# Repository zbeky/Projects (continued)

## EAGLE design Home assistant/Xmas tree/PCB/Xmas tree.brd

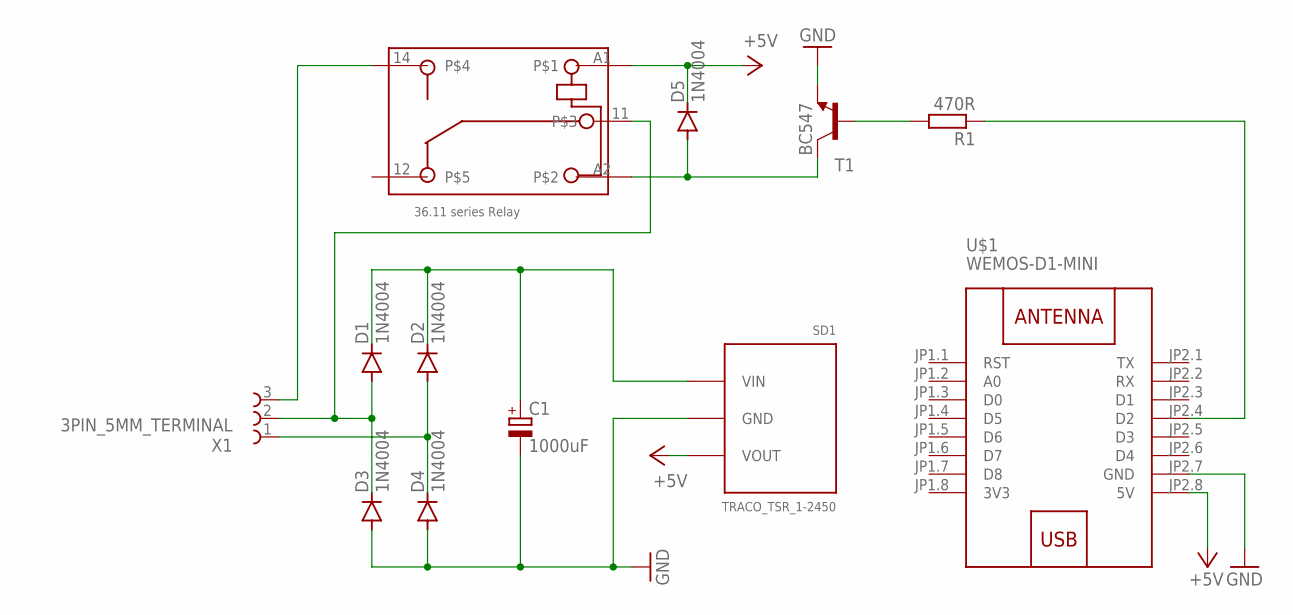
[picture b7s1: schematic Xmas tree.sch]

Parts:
C1: 1000uF; E3,5-10
D1, D2, D3, D4, D5: 1N4004; DO41-10
R1: 470R; 0207/10
RL1: 36.11
SD1: TRACO_TSR_1-2450
T1: BC547; TO92-CBE
U$1: WEMOS-D1-MINI
X1: 3PIN_5MM_TERMINAL

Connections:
3V3: U$1.JP1.8 (3V3)
12VDC: C1.+, D1.C, D2.C, SD1.VIN
+5V: D5.C, RL1.A1, SD1.VOUT, U$1.JP2.8 (5V)
+12VAC: D1.A, D3.C, RL1.11, X1.2
-12VAC: D2.A, D4.C, X1.1
GND: C1.-, D3.A, D4.A, SD1.GND, T1.E, U$1.JP2.7 (GND)
unnamed: R1.2, T1.B
unnamed: D5.A, RL1.A2, T1.C
unnamed: R1.1, U$1.JP2.4 (D2)
OUTPUT: RL1.14, X1.3

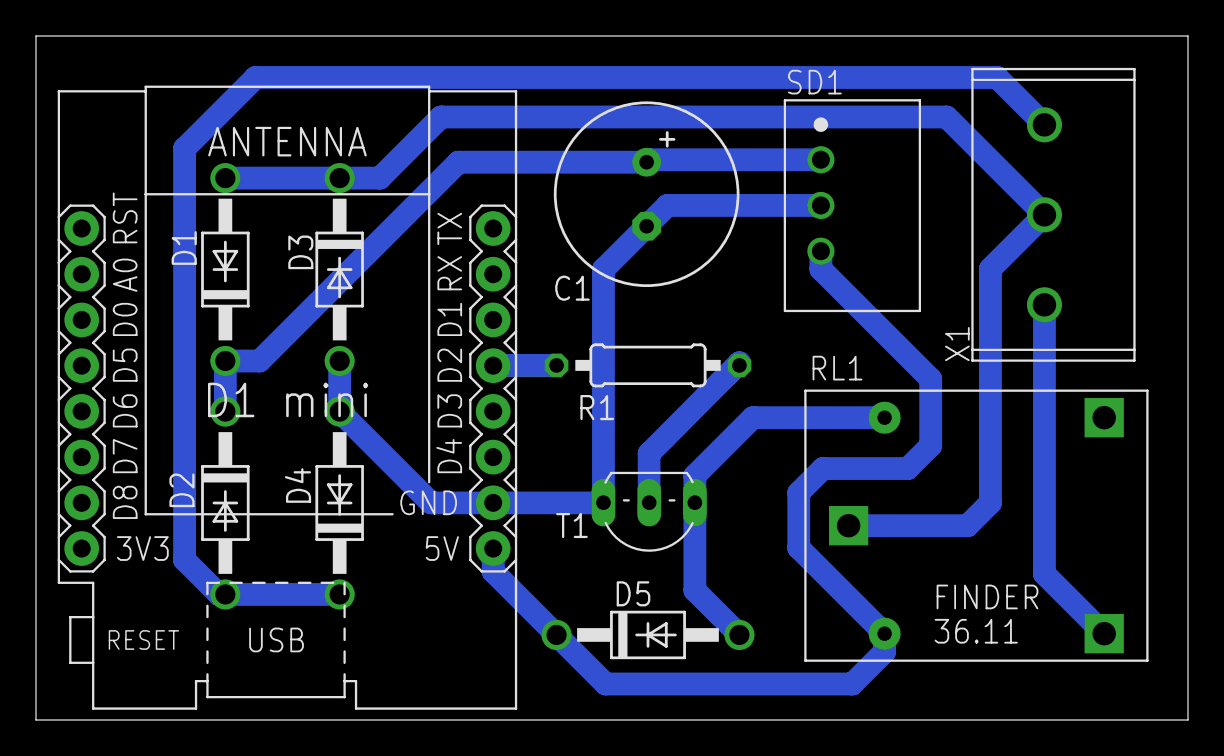
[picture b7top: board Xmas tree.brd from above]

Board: 2 copper layers, 64.0 x 38.0 mm, 12 parts (0 on the bottom side), 9 nets.

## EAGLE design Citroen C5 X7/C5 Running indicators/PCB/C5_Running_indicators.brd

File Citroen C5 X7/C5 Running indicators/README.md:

# Citroen C5 X7 front running indicators lights

- Universal PCB for up to 7 individually connected LEDs

## Parts:<br>
12 pieces 3W orange LED -https://www.aliexpress.com/item/4000321007733.html<br>
12 pieces LED lens - https://www.aliexpress.com/item/32790704606.html<br>
2 pieces step down - https://www.aliexpress.com/item/32826540392.html<br>

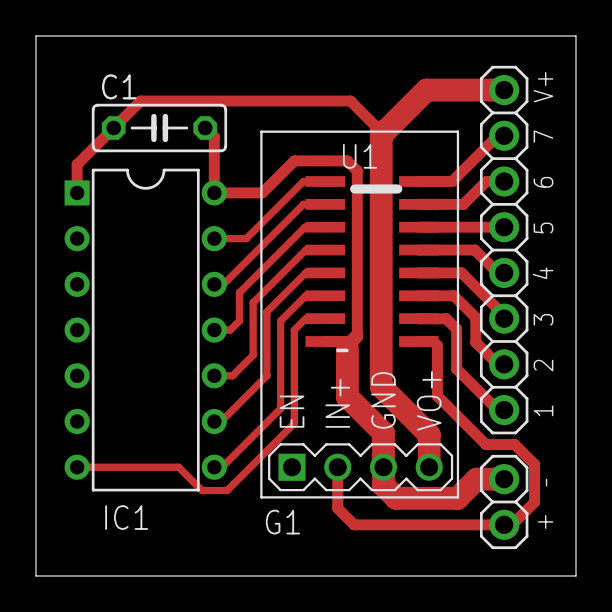
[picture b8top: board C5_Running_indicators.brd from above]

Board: 2 copper layers, 30.0 x 30.0 mm, 6 parts (0 on the bottom side), 17 nets.

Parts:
C1: 1uF; C050-025X075
G1: DC-DC-STEP-DOWN-MINI; DC-DC-DOWN-MINI
IC1: ATTINY84A-PU; DIL14
U1: TPL7407LDR; SOIC16N
X1: PINHD-1X2; 1X02
X2: 1X08

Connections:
+12V: G1.2, U1.9, X1.2
GND: C1.2, G1.3, IC1.14, U1.8, X1.1
unnamed: IC1.13, U1.1
unnamed: IC1.12, U1.2
unnamed: IC1.11, U1.3
unnamed: IC1.10, U1.4
unnamed: IC1.9, U1.5
unnamed: IC1.8, U1.6
unnamed: IC1.7, U1.7
unnamed: U1.10, X2.1
unnamed: U1.11, X2.2
unnamed: U1.12, X2.3
unnamed: U1.13, X2.4
unnamed: U1.14, X2.5
unnamed: U1.15, X2.6
unnamed: U1.16, X2.7
VDD: C1.1, G1.4, IC1.1, X2.8

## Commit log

2020-11-09 Xmas tree update
2020-11-09 Include libraries
2020-11-09 Fingerprint opener
2020-11-09 Fingerprint
2020-11-12 Add 3D printed case
2020-11-12 Enable FET on startup
2020-11-13 Updated PCB
2020-11-15 Add ESPHome 4way light switch
2020-11-15 New gerber
2020-11-25 Add Lenovo M10 docking station
2020-11-26 Fingerprint update
2020-12-01 Don't block fingeprint by lost connection
2020-12-01 Capital letters
2020-12-04 Fix capacitor value
2020-12-07 Add schematic for fingerprint
2020-12-11 Triac christmass tree
2020-12-14 4way switch update
2021-01-14 Fingerprint sensor reset function
2021-03-19 C5 Running indicators and ATTiny85 PWM shift
2021-03-23 Add new projects
2021-03-25 Add operating states to cover
2021-05-21 Filter noise
2021-11-09 Add Peugeot 3008 High beams dimming
2023-10-23 Add ESPHome 4ch CCT LED driver
2023-12-10 Add 6ch esphome led driver
2023-12-12 Fix USB
2024-03-25 Fix boot mode
2024-04-14 Add windows blinds V2 PCB
2024-08-13 Add V2 covers
2025-12-06 Cleanup
